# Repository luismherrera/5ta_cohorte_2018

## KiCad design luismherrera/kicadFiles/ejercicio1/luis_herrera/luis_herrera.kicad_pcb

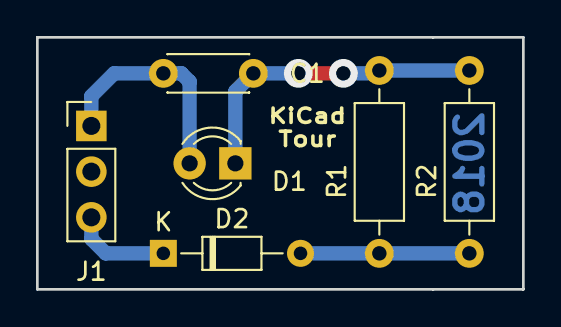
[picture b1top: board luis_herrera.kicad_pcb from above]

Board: 2 copper layers, 27.0 x 14.0 mm, 6 parts (0 on the bottom side), 4 nets.

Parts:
C1: C; C_Disc_D4.3mm_W1.9mm_P5.00mm
D1: LED; LED_D3.0mm
D2: D; D_DO-34_SOD68_P7.62mm_Horizontal
J1: Conn_01x03; PinHeader_1x03_P2.54mm_Vertical
R1, R2: R; R_Axial_DIN0207_L6.3mm_D2.5mm_P10.16mm_Horizontal

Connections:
unnamed: C1.1, D1.1, R1.2, R2.2
unnamed: C1.2, D1.2, J1.1
unnamed: D2.1, J1.3
unnamed: D2.2, R1.1, R2.1

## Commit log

2018-09-04 Se agregan archivos de KiCad - Ejercicio 1
2018-09-07 KiCad Ejercicio 1 - Se finaliza con ubicación de componentes y ruteo. Placa finalizada
